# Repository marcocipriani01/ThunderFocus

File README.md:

# ThunderFocus

ThunderFocus is an open-source telescope focuser developed by Marco Cipriani. The source code is available on [GitHub](https://github.com/marcocipriani01/ThunderFocus) and is issued under the [GNU General Public License version 3](https://www.gnu.org/licenses/gpl-3.0.html).

## Showcase of controllers and focusers [on my website](https://marcocipriani01.github.io/projects/ThunderFocus)!

## Description of the project

ThunderFocus is an all-in-one focuser and power box (dew heater controller) designed to be fully customizable and feature-rich. It has its own control software written in Java and is both [INDI](https://indilib.org/) and [ASCOM](https://ascom-standards.org/) compatible.

The firmware can run on both Arduino and Teensy, with the only difference being the RTC support and the speed of the MCU. Thanks to the firmware configuration file, you can select only the features you need and remove the unnecessary: the control software will detect the available features and display only the options supported by the board, so you won't need to modify other files.

The user interface is platform-independent and works seamless across computers and boards like Raspberry Pi, with the only requirement being Java 15 (bundled in the Windows installer): in this way, you get the same experience no matter what OS you run. Moreover, it uses [INDIForJava](http://indiforjava.sourceforge.net/stage/index.html) for INDI/KStars compatibility and a special ASCOM driver for Windows compatibility. As a bonus, it can also be controlled using the [Telescope.Touch Android app](https://github.com/marcocipriani01/Telescope.Touch) when the INDI server is enabled!

## Features

- INDI/ASCOM compatibility, cross platform interface
- Full telescope focuser control
  - Can control either one main telescope focuser or one guidescope/off-axis guider focuser
  - Backlash compensation
  - Precise micro-stepping control for pin-point stars
  - Displays the focuser position in millimeters, ticks or any unit of your liking
  - Remembers the last position
- Advanced dew heaters control, which can also turn on and off the telescope mount or other accessories.
  - Various automatic modes: temperature, dew point, humidity, sunset/sunrise
  - Manual control/override of outputs
  - Completely autonomous after configuration: can work without a PC
  - Restores the last state after power up
  - High efficiency, does not require heatsinks or cooling
- Ambient monitoring
  - Temperature, humidity, dew point
  - Graphs of the whole observing night

## Installing the software

### Windows x64

Get [the latest release](https://github.com/marcocipriani01/ThunderFocus/releases) and install it. You're done!

### Debian, Ubuntu and Raspberry Pi OS

**Skip the Java installation if you already have it installed!**

Install the latest Java Development Kit available, version 17 or greater. On Ubuntu:

- `sudo apt update`
- `sudo apt install openjdk-17-jdk`

Raspberry Pi OS or Astroberry:

- Download the latest [Eclipse Temurin build](https://adoptium.net/temurin/releases/) JRE or JDK (recommended: version 17, HotSpot JVM)
- Run `sudo mkdir /usr/java/`
- Extract the archive using `sudo tar -zxf OpenJDK17_RELEASE.tar.gz -C /usr/java/` (change the filename accordingly to what you downloaded)
- Run `echo 'export PATH=$PATH:/usr/java/' | sudo tee -a /etc/profile`

### macOS, Windows 32-bit and other Linux distros

Install Java version 17 or greater and then use the `.jar` ThunderFocus release.

## Development

### Building the firmware

1. Install [Visual Studio Code](https://code.visualstudio.com/) and the [PlatformIO](https://platformio.org/install/ide?install=vscode) extension
2. Install the Arduino or Teensy core in the PlatformIO boards manager
3. Open the `ThunderFocus-firmware` folder inside VS Code
4. Select the PlatformIO Project Environment (`nanoatmega328`, `teensy40`, etc) from the status bar, or add a custom one in `platformio.ini`
5. Open `src/config.h` and enable **one and only one** board config file
6. Open the configuration file you enabled and make the appropriate changes (comments in the file will guide you)
   - Select the pins according to your circuit
   - Enable or disable features
   - Eventual errors or incompatible combinations of features will stop the compilation
7. Done! Upload the firmware

### Building the control software `jar` files

1. Install a [Java Development Kit](https://www.oracle.com/java/technologies/javase-downloads.html), version 15 or greater
2. Install [IntelliJ IDEA community](https://www.jetbrains.com/idea/)
3. Open `ThunderFocus-GUI` inside IntelliJ
4. Just run the only configuration in the project, it will build the artifacts for you and place them in the right places

### Creating the Windows installer

Requires the `jar` files. Make sure to follow the previous step.

1. Install [Inno Setup](https://jrsoftware.org/isinfo.php) and [Visual Studio](https://visualstudio.microsoft.com/it/) with Visual Basic .NET support
2. Open `ASCOM.ThunderFocus` inside Visual Studio
3. Compile the _Release_ configuration (do not run it)
4. Extract a copy of the [AdoptOpenJDK](https://adoptopenjdk.net/releases.html) in the `JRE-bundle` folder
    - Recommended: _OpenJDK 15_ with _HotSpot VM_, Windows x64
5. Open `InnoSetup.iss` and make the necessary changes to the file:
    - Replace `D:\ThunderFocus\` with the path to the ThunderFocus repository in your computer
6. Compile and run the Inno Setup file: it will create the Windows installer in the `Installers` folder

### Creating the Debian package

Requires the `jar` files and a Debian installation with `dpkg-deb`. Note: the Debian package will not include a bundled JDK. Make sure to install it and make the necessary changes to the `PATH` env variable.

1. Run `cd ThunderFocus-GUI/deb-builder`
2. `./build.sh` (requires `root` access to set the appropriate permissions)
3. You're done, the installer will be located in the usual `Installers` folder

## Used libraries

- [Eclipse Temurin](https://adoptium.net/) by The Eclipse Foundation, [GPL v2 license with classpath exception](https://openjdk.java.net/legal/gplv2+ce.html)
- [INDIForJava](https://indiforjava.github.io/) by Marco Cipriani, Sergio Alonso and Richard van Nieuwenhoven, [LGPL v3 license](https://github.com/INDIForJava/INDIForJava-core/blob/main/LICENSE.txt)
- [ASCOM .NET libraries](https://www.ascom-standards.org/) by The ASCOM Initiative, [ASCOM Open Source License](https://github.com/ASCOMInitiative/ASCOMPlatform/blob/master/LICENSE.txt)
- [jssc](https://github.com/java-native/jssc) by java-native and scream3r, [LGPL v3 license](https://github.com/java-native/jssc/blob/master/LICENSE.txt)
- [FlatLaf](https://github.com/JFormDesigner/FlatLaf/) by JFormDesigner, [Apache 2.0 license](https://github.com/JFormDesigner/FlatLaf/blob/master/LICENSE)
- [Gson](https://github.com/google/gson) by Google, [Apache 2.0 license](https://github.com/google/gson/blob/master/LICENSE)
- [Material icons](https://material.io/resources/icons/) by Google, [Apache 2.0 license](https://www.apache.org/licenses/LICENSE-2.0.html)
- [Arduino Core APIs](https://github.com/arduino/Arduino) by Arduino, [LGPL v3 license](https://github.com/arduino/Arduino/blob/master/license.txt)
- [AccelStepper](https://www.airspayce.com/mikem/arduino/AccelStepper/) by Mike McCauley (with modifications), [GPL v3 license](https://www.gnu.org/licenses/gpl-3.0.html)
- [Arduino Time Library](https://github.com/PaulStoffregen/Time) by Michael Margolis, [LGPL v2.1 license](https://www.gnu.org/licenses/old-licenses/lgpl-2.1.html)
- [Adafruit BME280 Library](https://github.com/adafruit/Adafruit_BME280_Library) by Adafruit Industries, [3-Clause BSD license](https://github.com/adafruit/Adafruit_BME280_Library/blob/master/LICENSE.md)
- [Adafruit HTU21D-F Library](https://github.com/adafruit/Adafruit_HTU21DF_Library) by Adafruit Industries
- [SolarPosition library](https://github.com/KenWillmott/SolarPosition) by Ken Willmott
  - Based on [_Arduino Uno and Solar Position Calculations_](http://www.instesre.org/ArduinoDocuments.htm), © David R. Brooks, issued under the [Creative Commons Attribution-NonCommercial-NoDerivatives 4.0 International License](https://creativecommons.org/licenses/by-nc-nd/4.0/)
  - Uses equations from the book [_Astronomical Algorithms_ by Jean Meeus](https://www.willbell.com/math/mc1.HTM), published by Willmann-Bell, Inc., Richmond, VA
- [Telescope icon](https://www.flaticon.com/free-icon/telescope_547425?term=telescope&page=1&position=9&related_item_id=547425) by Freepik, [Flaticon license](https://www.freepikcompany.com/legal#nav-flaticon)

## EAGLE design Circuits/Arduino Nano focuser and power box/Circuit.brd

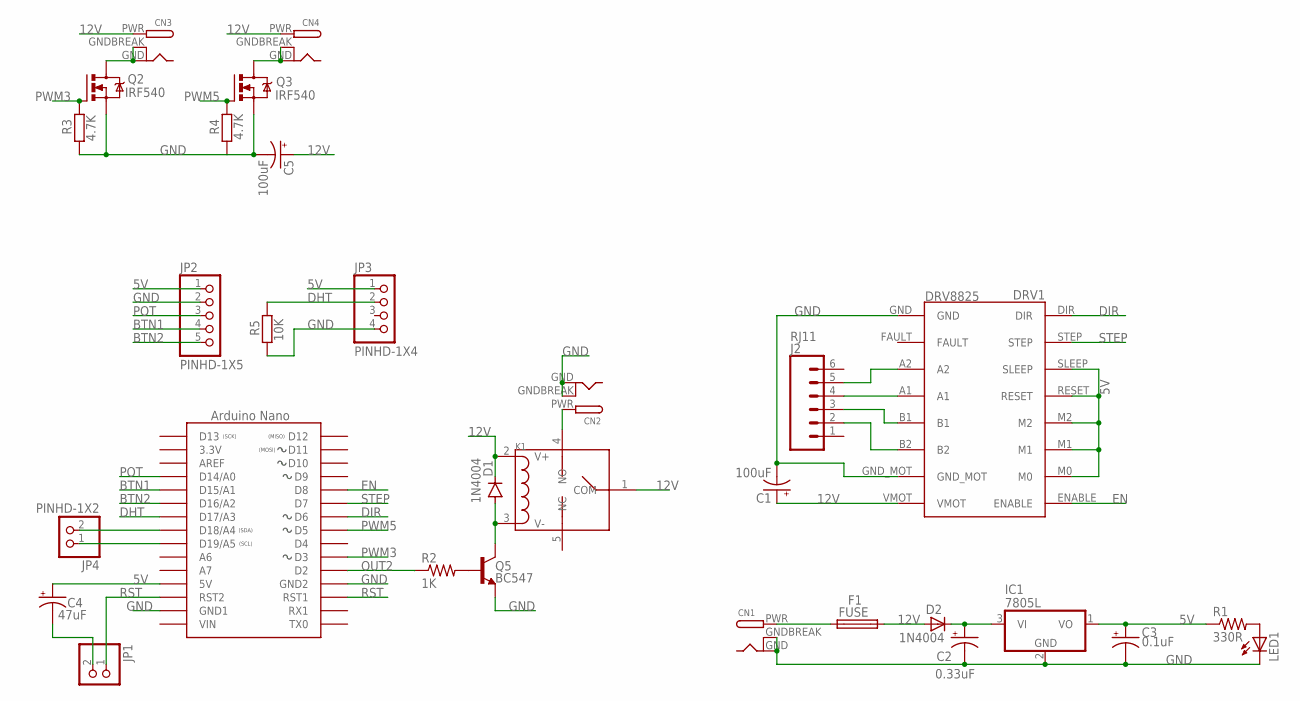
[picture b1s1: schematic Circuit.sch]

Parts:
C1, C5: 100uF; E2,5-6
C2: 0.33uF; E2-5
C3: 0.1uF; E2-5
C4: 47uF; E2,5-6
CN1, CN2, CN3, CN4: DCBARRELPTH; DCJACK_2MM_PTH
D1, D2: 1N4004; DO41-10
DRV1: DRV8825
F1: FUSE; SH22,5
IC1: 7805L; TO92
J2: RJ11; RJ11-6
JP1, JP4: PINHD-1X2; 1X02
JP2: PINHD-1X5; 1X05
JP3: PINHD-1X4; 1X04
K1: RELAY-HLS8L-DC5V-S-CHLS8L-DC5V-S-C; REY5-19.0X15.0X15.0MM
LED1: LED5MM
Q2, Q3: IRF540; TO220BV
Q5: BC547; TO-92
R1: 330R; 0204/7
R2: 1K; 0204/7
R3, R4: 4.7K; 0204/5
R5: 10K; 0204/5
U$1: NANO

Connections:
5V: C3.+, C4.+, DRV1.M0, DRV1.M1, DRV1.M2, DRV1.RESET, DRV1.SLEEP, IC1.1 (VO), JP2.1, JP3.1, R1.1, U$1.5V
12V: C1.+, C5.+, CN3.PWR, CN4.PWR, D1.C, D2.A, DRV1.VMOT, F1.2, K1.1 (COM), K1.2 (V+)
BTN1: JP2.4, U$1.A1 (D15/A1)
BTN2: JP2.5, U$1.A2 (D16/A2)
DHT: JP3.2, R5.2, U$1.A3 (D17/A3)
DIR: DRV1.DIR, U$1.D6
EN: DRV1.ENABLE, U$1.D8
GND: C1.-, C2.-, C3.-, C5.-, CN1.GND, CN1.GNDBREAK, CN2.GND, CN2.GNDBREAK, DRV1.GND, DRV1.GND_MOT, IC1.2 (GND), JP2.2, JP3.4, LED1.K (C), Q2.S, Q3.S, Q5.1 (E), R3.1, R4.1, R5.1, U$1.GND (GND1), U$1.GND1 (GND2)
unnamed: LED1.A, R1.2
unnamed: Q5.2 (B), R2.2
unnamed: CN2.PWR, K1.4 (NO)
unnamed: JP4.2, U$1.A4 (D18/A4)
unnamed: DRV1.A1, J2.4
unnamed: D1.A, K1.3 (V-), Q5.3 (C)
unnamed: JP4.1, U$1.A5 (D19/A5)
unnamed: C4.-, JP1.2
unnamed: DRV1.B2, J2.2
unnamed: DRV1.B1, J2.3
unnamed: DRV1.A2, J2.5
unnamed: CN1.PWR, F1.1
unnamed: CN3.GND, CN3.GNDBREAK, Q2.D
unnamed: CN4.GND, CN4.GNDBREAK, Q3.D
unnamed: C2.+, D2.C, IC1.3 (VI)
OUT2: R2.1, U$1.D2
POT: JP2.3, U$1.A0 (D14/A0)
PWM3: Q2.G, R3.2, U$1.D3
PWM5: Q3.G, R4.2, U$1.D5
RST: JP1.1, U$1.RST (RST2), U$1.RST1
STEP: DRV1.STEP, U$1.D7

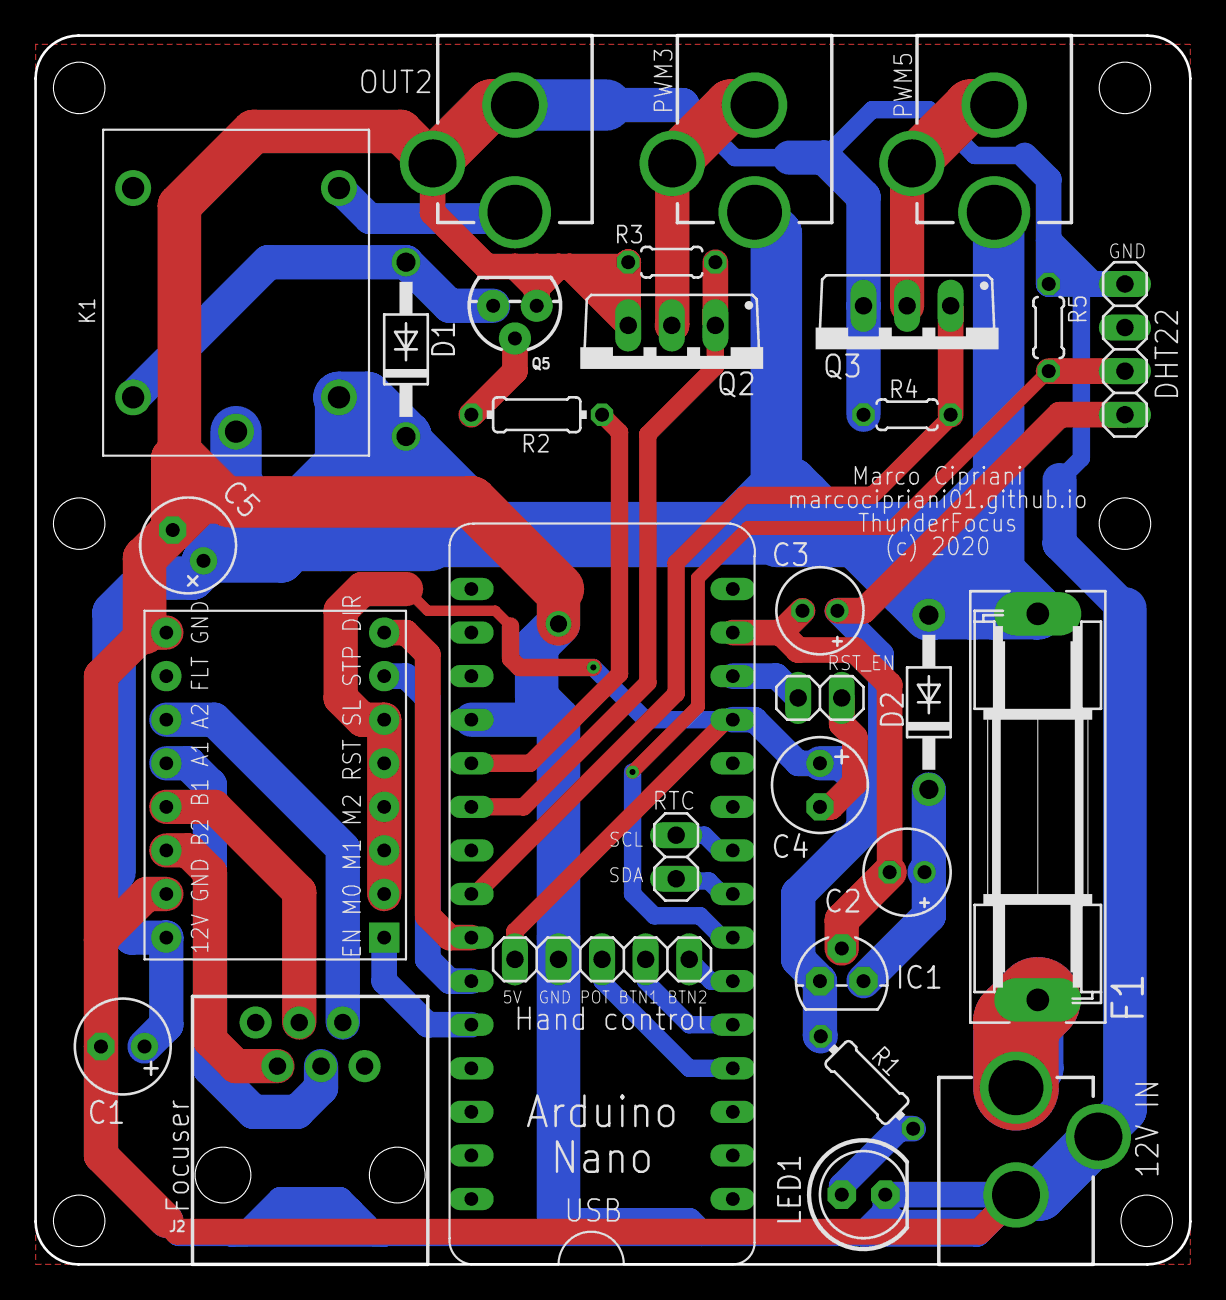
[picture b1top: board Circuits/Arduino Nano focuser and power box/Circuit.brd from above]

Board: 2 copper layers, 67.3 x 71.6 mm, 30 parts (0 on the bottom side), 29 nets.

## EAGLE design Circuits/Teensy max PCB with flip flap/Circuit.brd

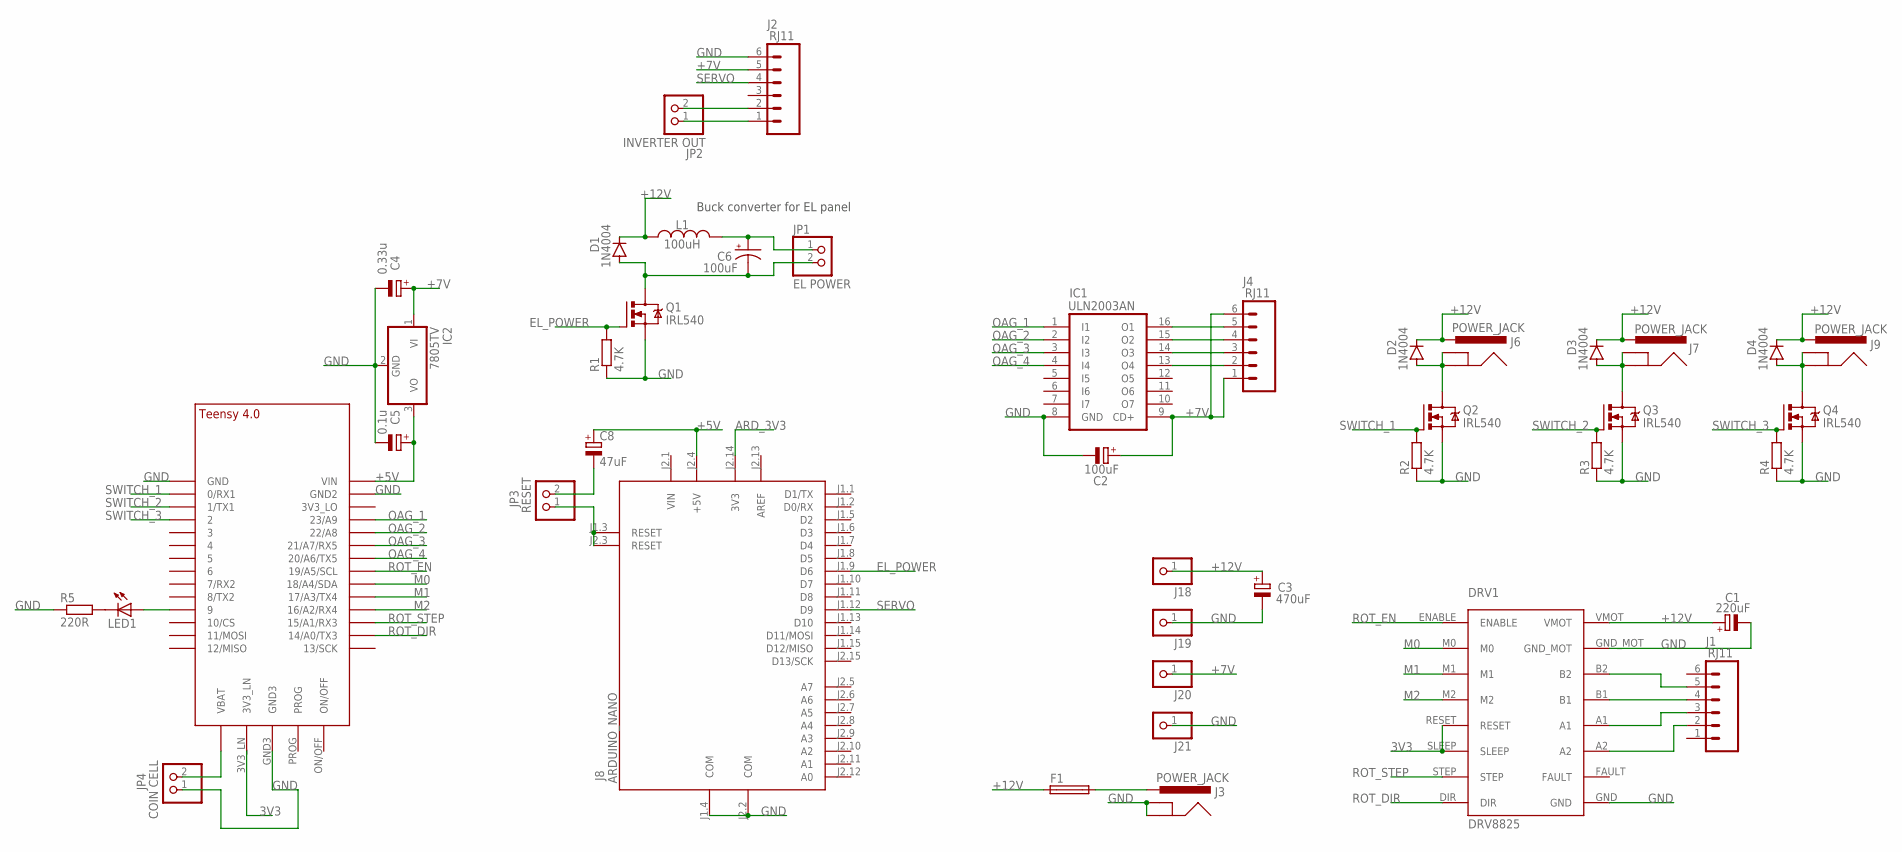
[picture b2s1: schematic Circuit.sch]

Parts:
C1: 220uF; E3,5-8
C2: 100uF; E2,5-6
C3: 470uF; E3,5-8
C4: 0.33u; E1,8-4
C5: 0.1u; E1,8-4
C6: 100uF; E2,5-7
C8: 47uF; E2,5-6E
D1, D2, D3, D4: 1N4004; DO41-10
DRV1: DRV8825
F1: SH22,5
IC1: ULN2003AN; DIL16
IC2: 7805TV; TO220V
J1, J2, J4: RJ11; RJ11-6
J3, J6, J7, J9: POWER_JACK; POWER_JACK_PTH
J8: ARDUINO_NANO; ARDUINO_NANO2
J18, J19, J20, J21: PINHD-1X1; 1X01
JP1: EL POWER; 1X02
JP2: INVERTER OUT; 1X02
JP3: RESET; 1X02
JP4: COIN CELL; 1X02
L1: 100uH; 6000-XXXX-RC
LED1: LED3MM
Q1, Q2, Q3, Q4: IRL540; TO220BV
R1, R2, R3, R4: 4.7K; 0204/7
R5: 220R; 0204/5
U$1: TEENSY_4.0-BASIC

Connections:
3V3: DRV1.RESET, DRV1.SLEEP, U$1.3V3_LN
+5V: C5.+, C8.+, IC2.3 (VO), J8.J2.4 (+5V), U$1.VIN
+7V: C2.+, C4.+, IC1.9 (CD+), IC2.1 (VI), J2.5, J4.1, J4.6, J20.1
+12V: C1.+, C3.+, D1.C, D2.C, D3.C, D4.C, DRV1.VMOT, F1.1, J6.PWR, J7.PWR, J9.PWR, J18.1, L1.1
ARD_3V3: J8.J2.14 (3V3)
AREF: J8.J2.13 (AREF)
EL_POWER: J8.J1.9 (D6), Q1.G, R1.2
GND: C1.-, C2.-, C3.-, C4.-, C5.-, DRV1.GND, DRV1.GND_MOT, IC1.8 (GND), IC2.2 (GND), J2.6, J3.GND, J3.GNDBREAK, J8.J1.4 (COM), J8.J2.2 (COM), J19.1, J21.1, JP4.1, Q1.S, Q2.S, Q3.S, Q4.S, R1.1, R2.1, R3.1, R4.1, R5.1, U$1.GND, U$1.GND2, U$1.GND3
M0: DRV1.M0, U$1.18/A4/SDA
M1: DRV1.M1, U$1.17/A3 (17/A3/TX4)
M2: DRV1.M2, U$1.16/A2 (16/A2/RX4)
unnamed: DRV1.B1, J1.4
unnamed: D3.A, J7.GND, J7.GNDBREAK, Q3.D
unnamed: C6.-, D1.A, JP1.2, Q1.D
unnamed: D4.A, J9.GND, J9.GNDBREAK, Q4.D
unnamed: D2.A, J6.GND, J6.GNDBREAK, Q2.D
unnamed: DRV1.B2, J1.5
unnamed: IC1.16 (O1), J4.5
unnamed: DRV1.A1, J1.3
unnamed: DRV1.A2, J1.2
unnamed: LED1.A, U$1.9/CS (9)
unnamed: LED1.K (C), R5.2
unnamed: C6.+, JP1.1, L1.2
unnamed: J2.1, JP2.1
unnamed: J2.2, JP2.2
unnamed: JP4.2, U$1.VBAT\ (VBAT)
unnamed: IC1.15 (O2), J4.4
unnamed: IC1.14 (O3), J4.3
unnamed: IC1.13 (O4), J4.2
unnamed: J8.J1.3 (RESET), J8.J2.3 (RESET), JP3.1
unnamed: C8.-, JP3.2
unnamed: F1.2, J3.PWR
OAG_1: IC1.1 (I1), U$1.23/A9
OAG_2: IC1.2 (I2), U$1.22/A8
OAG_3: IC1.3 (I3), U$1.21/A7 (21/A7/RX5)
OAG_4: IC1.4 (I4), U$1.20/A6 (20/A6/TX5)
ROT_DIR: DRV1.DIR, U$1.14/A0 (14/A0/TX3)
ROT_EN: DRV1.ENABLE, U$1.19/A5/SCL
ROT_STEP: DRV1.STEP, U$1.15/A1 (15/A1/RX3)
SERVO: J2.4, J8.J1.12 (D9)
SWITCH_1: Q2.G, R2.2, U$1.0/RX (0/RX1)
SWITCH_2: Q3.G, R3.2, U$1.1/TX (1/TX1)
SWITCH_3: Q4.G, R4.2, U$1.2
VIN: J8.J2.1 (VIN)

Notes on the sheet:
Buck converter for EL panel

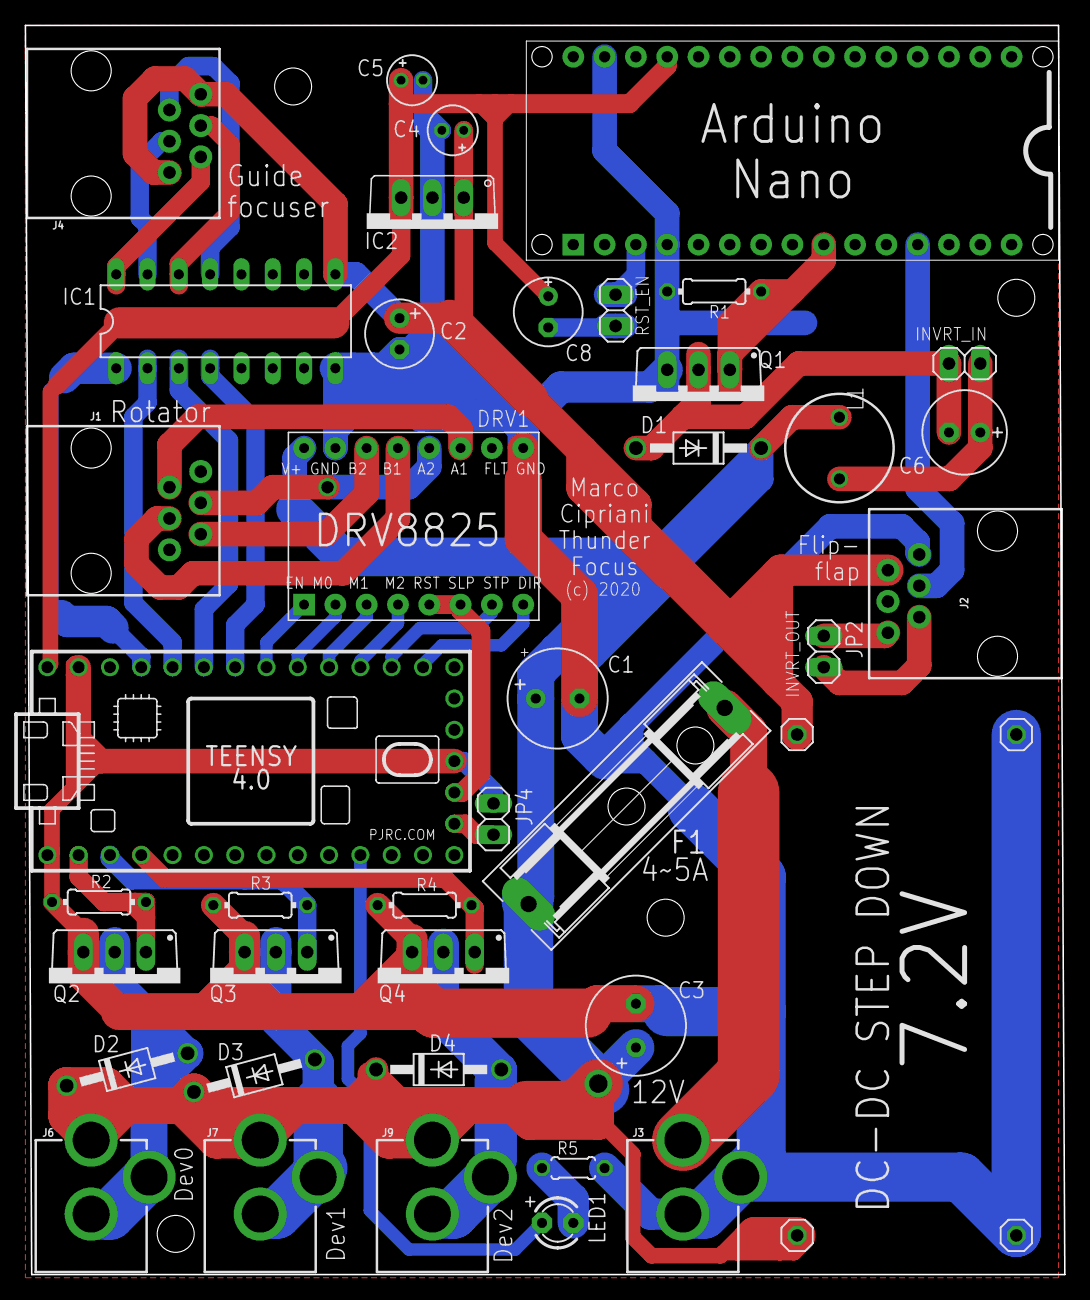
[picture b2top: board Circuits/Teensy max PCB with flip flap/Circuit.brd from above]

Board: 2 copper layers, 84.3 x 101.3 mm, 43 parts (0 on the bottom side), 41 nets.

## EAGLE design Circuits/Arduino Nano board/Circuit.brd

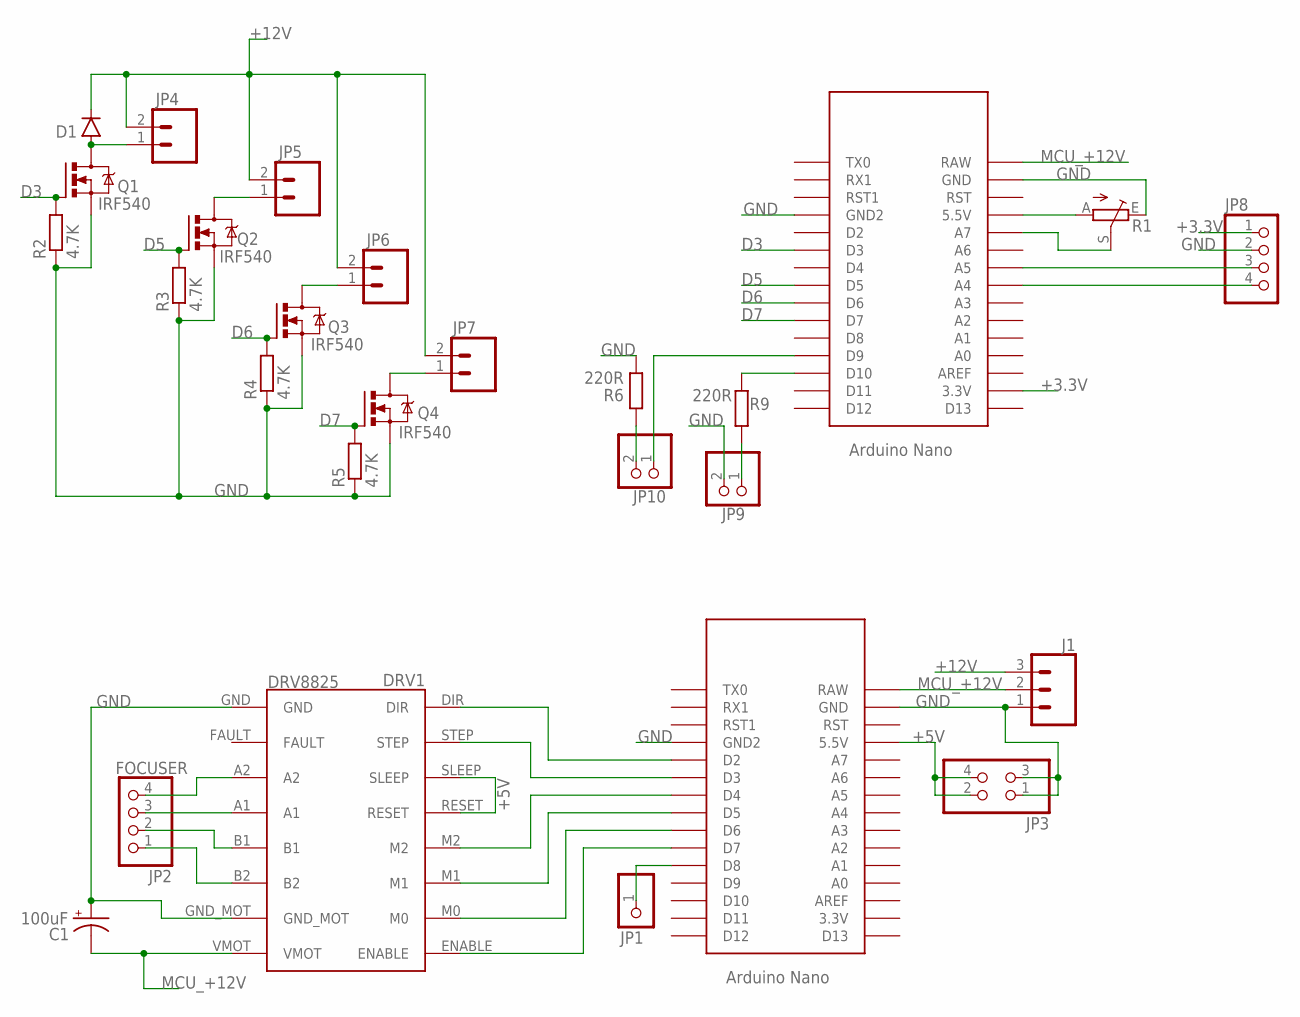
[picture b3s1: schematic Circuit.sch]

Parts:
C1: 100uF; B45181A
D1: DIODE1N4148; DIODE-1N4148
DRV1: DRV8825
J1: CONN_03-SCREW-5MM; SCREWTERMINAL-5MM-3
JP1: PINHD-1X1; 1X01
JP2: FOCUSER; 1X04
JP3: PINHD-2X2; 2X02
JP4, JP5, JP6, JP7: GREEN-2P-5.0; SCREWTERMINAL-5MM-2
JP8: PINHD-1X4; 1X04
JP9, JP10: PINHD-1X2; 1X02
Q1, Q2, Q3, Q4: IRF540; TO220BV
R1: TRIM_EU-B64Y; B64Y
R2, R3, R4, R5: 4.7K; 0204/5
R6, R9: 220R; 0204/5
U$1, U$3: NANO

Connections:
+3.3V: JP8.1, U$3.3.3V
+5V: DRV1.RESET, DRV1.SLEEP, JP3.2, JP3.4, U$1.5V (5.5V)
+12V: D1.C, J1.3, JP4.2, JP5.2, JP6.2, JP7.2
D3: Q1.G, R2.2, U$3.D3
D5: Q2.G, R3.2, U$3.D5
D6: Q3.G, R4.2, U$3.D6
D7: Q4.G, R5.2, U$3.D7
GND: C1.+, DRV1.GND, DRV1.GND_MOT, J1.1, JP3.1, JP3.3, JP8.2, JP9.2, Q1.S, Q2.S, Q3.S, Q4.S, R1.E, R2.1, R3.1, R4.1, R5.1, R6.2, U$1.GND, U$1.GND1 (GND2), U$3.GND, U$3.GND1 (GND2)
MCU_+12V: C1.-, DRV1.VMOT, J1.2, U$1.RAW, U$3.RAW
unnamed: DRV1.ENABLE, U$1.D7
unnamed: JP7.1, Q4.D
unnamed: R1.A, U$3.5V (5.5V)
unnamed: JP1.1, U$1.D8
unnamed: DRV1.DIR, U$1.D2
unnamed: D1.A, JP4.1, Q1.D
unnamed: JP10.2, R6.1
unnamed: JP10.1, U$3.D9
unnamed: R9.2, U$3.D10
unnamed: JP8.4, U$3.A4
unnamed: DRV1.STEP, U$1.D3
unnamed: DRV1.B2, JP2.1
unnamed: DRV1.B1, JP2.2
unnamed: DRV1.A1, JP2.3
unnamed: DRV1.A2, JP2.4
unnamed: DRV1.M2, U$1.D4
unnamed: DRV1.M1, U$1.D5
unnamed: DRV1.M0, U$1.D6
unnamed: JP5.1, Q2.D
unnamed: JP8.3, U$3.A5
unnamed: JP6.1, Q3.D
unnamed: JP9.1, R9.1
unnamed: R1.S, U$3.A7

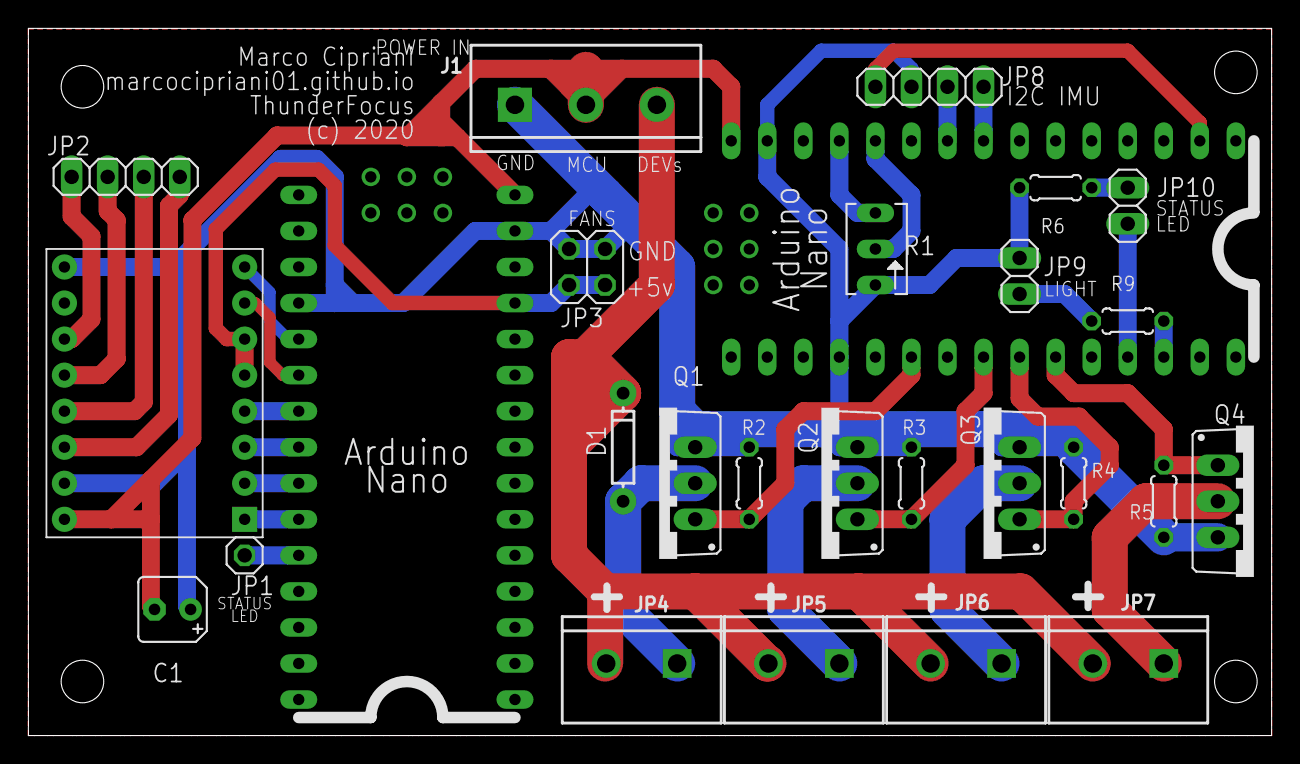
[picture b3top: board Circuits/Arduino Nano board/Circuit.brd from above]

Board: 2 copper layers, 87.6 x 49.8 mm, 27 parts (0 on the bottom side), 32 nets.

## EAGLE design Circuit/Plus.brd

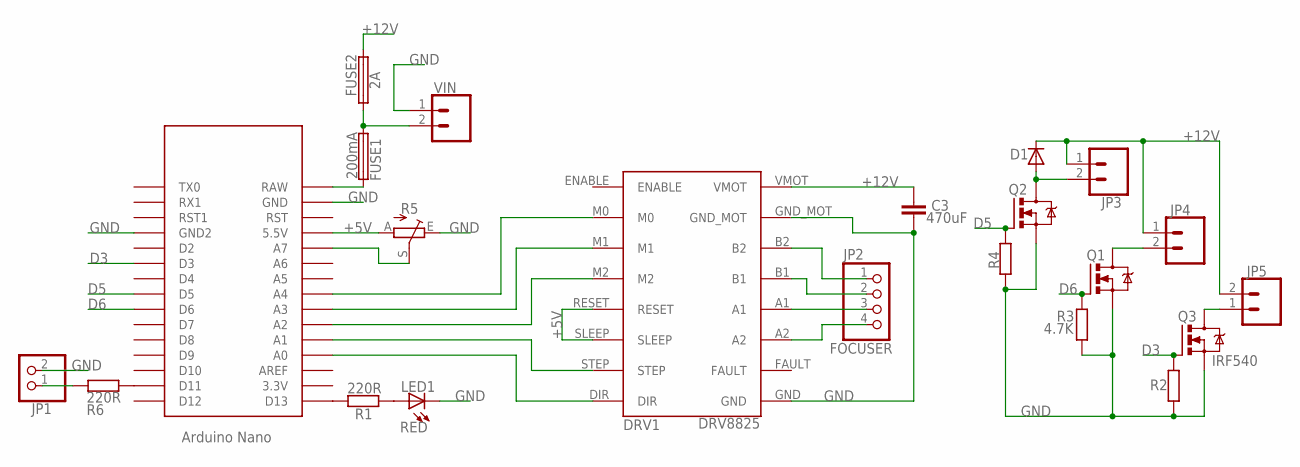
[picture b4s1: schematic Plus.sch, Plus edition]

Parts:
C3: 470uF; C5B2.5
D1: DIODE-D-2.5; D-2.5
DRV1: DRV8825
FUSE1: 200mA; FUSE_HOLDER_5X20MM
FUSE2: 2A; FUSE_HOLDER_5X20MM
JP1: PINHD-1X2; 1X02
JP2: FOCUSER; 1X04
JP3, JP4, JP5: CONN_025MM; SCREWTERMINAL-5MM-2
LED1: RED; LED3MM
Q1, Q2, Q3: IRF540; TO220BV
R1, R6: 220R; 0204/5
R2, R3, R4: 4.7K; 0204/5
R5: TRIM_EU-B64Y; B64Y
U$1: NANO
VIN: CONN_025MM; SCREWTERMINAL-5MM-2

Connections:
+5V: DRV1.RESET, DRV1.SLEEP, R5.A, U$1.5V (5.5V)
+12V: C3.2, D1.C, DRV1.VMOT, FUSE2.2, JP3.1, JP4.1, JP5.2
D3: Q3.G, R2.2, U$1.D3
D5: Q2.G, R4.2, U$1.D5
D6: Q1.G, R3.2, U$1.D6
D13: R1.2, U$1.D13
GND: C3.1, DRV1.GND, DRV1.GND_MOT, JP1.2, LED1.K (C), Q1.S, Q2.S, Q3.S, R2.1, R3.1, R4.1, R5.E, U$1.GND, U$1.GND1 (GND2), VIN.1
unnamed: LED1.A, R1.1
unnamed: R5.S, U$1.A7
unnamed: R6.2, U$1.D11
unnamed: FUSE1.2, U$1.RAW
unnamed: DRV1.DIR, U$1.A0
unnamed: JP5.1, Q3.D
unnamed: FUSE1.1, FUSE2.1, VIN.2
unnamed: D1.A, JP3.2, Q2.D
unnamed: JP4.2, Q1.D
unnamed: DRV1.STEP, U$1.A1
unnamed: DRV1.B2, JP2.1
unnamed: DRV1.B1, JP2.2
unnamed: DRV1.A1, JP2.3
unnamed: DRV1.A2, JP2.4
unnamed: DRV1.M2, U$1.A2
unnamed: DRV1.M1, U$1.A3
unnamed: JP1.1, R6.1
unnamed: DRV1.M0, U$1.A4

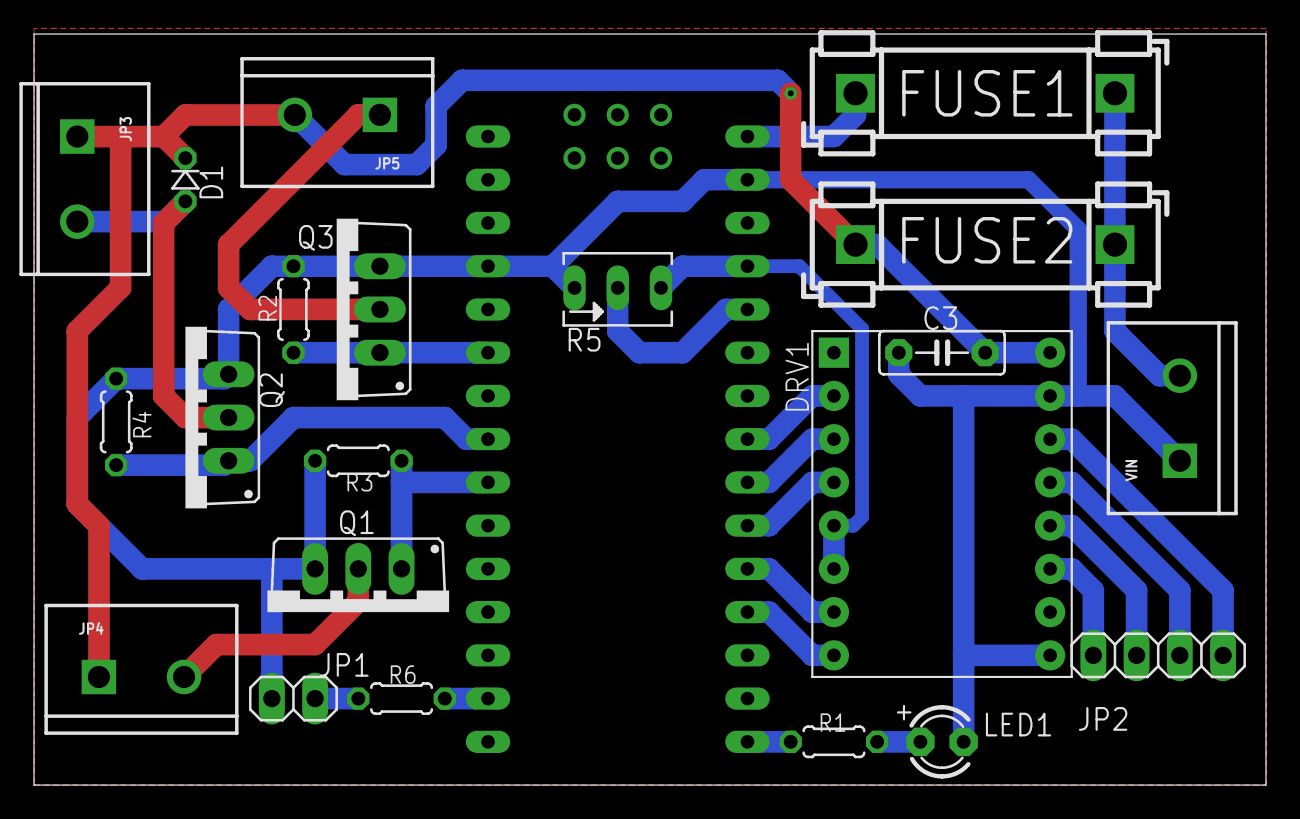
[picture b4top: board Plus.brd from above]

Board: 2 copper layers, 72.4 x 44.1 mm, 22 parts (0 on the bottom side), 25 nets.

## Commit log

2018-11-14 Inital commit
2019-01-09 README (en) update
2019-05-20 Refresh
2019-05-20 Optimize imports
2019-05-20 Fix launcher bug, lighter L&F
2019-05-21 Windows Serial Port Multiplexer pre-implementation in Java
2019-05-23 Bug fixing, added italian language
2019-05-23 Prepare for release
2019-05-23 Update files
2019-09-11 Bug fixing, new release
2019-09-11 New codename
2019-09-11 Fix bug when updating from Linux, update Debian package version
2019-09-30 Pushing the first commits for the new OpenFocuser! Experimental stuff!
2020-04-17 17 apr update
2020-05-24 Stuff
2020-10-28 Upload
2020-11-19 ThunderFocus!
2020-11-21 Update deb
2020-11-21 Update intallers
2020-11-21 Update README & res
2020-11-30 Experimental auto dew heaters
2020-11-30 Firmware done (hopefully). Added multi-configs
2020-12-01 Working PowerBox, automatic modes left to test
2020-12-04 Added charts, auto ambient mode works
2020-12-05 It works!
2020-12-06 Version 2.1 beta
2020-12-07 ASCOM driver working
2020-12-08 ASCOM completed and Inno Setup updated
2020-12-08 Fix compile bugs and update installer
2020-12-08 Update Debian package v2.2 fix
2020-12-16 Fix bugs, improve backlash calibration
2020-12-18 Update ASCOM driver
2020-12-18 Add gitignore
2020-12-20 Update misc, initial internationalization support
2020-12-20 i18n improvements
2020-12-21 I18N: english language completed
2020-12-21 Refresh circuits
2020-12-25 New circuit
2020-12-31 Moved INDIForJava to jar library
2021-01-01 Improvements, INDIForJava update
2021-01-01 Update version number
2021-01-01 Update to Java 15, fix browser bug
2021-01-01 Update to Java 15
2021-02-18 Bug fixing, new version, updated libraries, added debug mode
2021-02-18 Connection error details
2021-02-20 Automatic powerbox apply, crash fix
2021-03-04 Position calibrator
2021-03-04 Fix bug
2021-09-06 2.6.0 update: using Gradle for dependency resolving, updated libraries, improved powerbox manager with new features, small optimizations.
2021-09-06 Update README.md and Visual Studio files
2021-09-06 Update IntelliJ files
2021-09-08 Update INDIForJava
2021-11-19 Test
2021-11-19 Upload config
2021-11-22 No Focuser and HandController files
2021-11-22 Kinda working again
2021-11-22 Working
2021-11-25 Presets, save position, bug fixing
2021-11-25 Ready for release
2022-01-06 Import/export config
2022-01-13 Update Inno files
2022-01-15 Guidescope focuser
2022-01-30 BME280
2022-01-30 Fix pins
2022-05-10 New themes
2022-05-15 Firmware test update
2022-05-16 Compile successful
2022-05-22 Powerbox working
2022-05-24 Test new ASCOM driver
2022-05-25 ASCOM driver test
2022-05-27 ASCOM Switch kinda working
2022-05-27 Switch driver working
2022-05-28 ASCOM Conform all pass
2022-05-29 Remove old files, update README
2022-05-30 Update INDI driver
2022-06-01 Release candidate
2022-06-04 Fix test
2022-06-04 Fix ASCOM switch
2022-06-21 Fix firmware compile
2022-06-21 Hand controller
2022-08-13 Max travel w/ HC
2022-09-17 Update config
2022-12-10 New boards, ESP32 support
2023-01-18 Fix config
2023-08-10 DTR RTS control signals, update dependencies
2023-12-24 Java 21

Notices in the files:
Circuits/Arduino Nano board/Circuit.brd:
(c) 2020
parts and their libraries:
SparkFun-Connectors: Licensing: Creative Commons ShareAlike 4.0 International - https://creativecommons.org/licenses/by-sa/4.0
